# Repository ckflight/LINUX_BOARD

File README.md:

# Embedded Linux Board Running Custom Linux Distribution

### Project Info:

 * AT91SAM9N12 Microprocessor with Memory Management Unit based Embedded Linux Board hardware and operating system files.
It has 133 MHz RAM and 4 Gb NAND Flash and QSPI Flash Interfaces.

 * This design is the custom version of SAM9N12-EK. The custom design has a RAM with different speed and latency, also it is using NAND Flash as a memory. Therefore, AT91Bootstrap Hardware initialization files must be customized accordingly. Briefly, the PLL and clocking settings as well as RAM latency values and NAND interface pinouts are changed accordingly. To see the details of the changes, please check **LINUX_BOARD/Linux_Files/At91bootstrap Files/at91sam9n12ek.c and .h** files. 

 * Buildroot is used for custom linux distribution. Check step by step guide below for details. Follow Ubuntu, u-boot and buildroot versions strictly as indicated below to make it compile properly.

### Final Board Screenshots:

### Important Notes: 

 * Use TeraTerm on Windows or Picocom on Mac OSx to be able to set the baud rate to 118200 8bit no parity 1 stop. The reason of this baudrate is that, In AT91Bootstrap, cpu clock is configured from 400MHz to 300MHz for changing RAM speed from 133MHz to 100MHz. Since PLL multipliers are not strickly generating 300 and 100 MHz, the actual speeds are 301.333 MHz and 101.333. This main clock difference changes all other peripherals' clocking. As result of this, characters are not received correctly when the baudrate is set to 115200. When the baudrate is set to 118200 on HOST side, the hardware and the HOST side can talk without any issue. **(However in buildroot, u-boot and AT91Bootstrap files the uart is configured to 115200 8N1 no parity)**
 
 * The steps below are tested with UBUNTU 16.04.6 and 18.04.2 LTS.
 
### STEP BY STEP GUIDE FOR FLASHING BOARD TO RUN LINUX 
  
#### 1. This part describes how board is connected over USB and what commands needed to see on sam_ba program

   If linux board is new and fresh then connect over usb to linux virtual computer
   If linux board is flashed previously with files then connect nandflash's pin41 to ground and plug usb
   Linux will see device as /dev/ttyACM0 but sam_ba cannot see so type command (It is required every time): 
   
   	sudo chmod a+rw /dev/ttyACM0
   
   Or add read write permission to usb device to not write above command every time.To do that, 
   go to /etc/udev/rules.d and create a rule file such as myusb.rules file and add the line
 	
	sudo nano /etc/udev/rules.d/filename.rules
	KERNEL=="ttyACM[0-9]*",MODE="0666"

    Now sam-ba can see board as /dev/ttyACM0

#### 2. Before start install these libraries:

	1. sudo apt install libncurses5 libncursesw5-dev libncurses5-dev
	2. sudo apt install make
	3. sudo apt install gcc-arm-linux-gnueabi
	4. sudo apt install gcc
	5. sudo apt install g++
	6. sudo apt install python
        (these might no be needed)
	7. sudo apt install make-guile
	8. sudo apt install gcc-multilib
	9. sudo apt install gcc-arm*

	Files required for board and in this part they will be created:
	A. AT91SAMBOOTSTRAP 	(Initialises SAM9N12E hardware like clock, nano interface scram gpio etc.)
	B. U-BOOT    		(Initialises SAM9N12E hardware clk, ram and etc.)
	C. BUILDROOT 		(LINUX KERNEL + ROOTFS (Our python c compiler nano etc apps are in rootfs) )

#### 2.1 How to compile and create at91sambootstrap files:
 
   I put at91bootstrap-3-3.8.tar.gz, it is the latest version and works
   unzip to Ubuntu and use it. For any case download link is below:
	
	http://repository.timesys.com/buildsources/a/at91bootstrap-3/

   Go to at91bootstrap-3-3.8 folder and change 

 	/at91bootstrap-3-3.8/board/at91sam9n12ek/at91sam9n12ek.c and .h files
 
   with

 	/at91bootstrap Files/at91sam9n12ek.c and .h
 
   Go to the at91bootstrap-3-3.8 folder location over terminal and apply commands

	1. make mrproper

	2. make at91sam9n12eknf_uboot_defconfig (nf means it will be loaded to nandflash, and u-boot means it will run u-boot)

	3. make menuconfig 			(this will open a configuration window)
	   3.1.Go to RAM Configuration and change RAM size to 64M
	   3.2 Go to NAND Flash configuration and change PMECC Error Correction Bits to 4bits, Sector to 512
	   3.3 Go to U-Boot Image Storage Setup and change External Ram Address to Load U-Boot Image from
               0x26F00000 to 0x22000000
	   3.4 Save an Alternate File and it will create .config file in at91bootstrap-3-3.8.(It is invisible nano .config opens if needed.)

	4. make CROSS_COMPILE=arm-linux-gnueabi-

	RESULT: The at91sam9n12ek-nandflashboot-uboot-3.8-beta1.bin file is ready in binaries file

#### 2.2 How to compile and create u-boot files:

   I put u-boot-2015.1.tar.gz to folder no need to download newer versions since include files naming are changed
   and they are not compiling without error. Unzip it to Ubuntu and use. For any case download link is below:

	 http://repository.timesys.com/buildsources/u/u-boot/

   Go to folder and change

	u-boot-2015.01/board/atmel/at91sam9n12ek/at91sam9n12ek.c file 
	with 
	/u-boot Files/at91sam9n12ek.c

    and

	u-boot-2015.01/include/configs/at91sam9n12ek.h file 
	with	
	/u-boot Files/at91sam9n12ek.h
	
    also For Ubuntu 16.04 gcc5.h, For Ubuntu 18.04 gcc7.h add (they have same code inside as well)

	/u-boot Files/compiler-gcc5.h or gcc.7 file
	to
	u-boot-2015.01/include/linux folder

   Go to u-boot-2015.01 folder with terminal and apply commands

	1. make mrproper

	2. make at91sam9n12ek_nandflash_defconfig (nandflash means this file will be written to nandflash)

	3. make CROSS_COMPILE=arm-linux-gnueabi-

	RESULT: The u-boot.bin is in u-boot-2015.01 folder

#### 2.3 How to compile and create build root files:
   
   I put buildroot-2015.2.tar.gz to folder and this version works. For any case download link is below:

	https://buildroot.org/downloads/

   Before start: Buildroot might create errors during compile. 
                 These are mostly package version collision type errors.
                 I look for error file and try to correct them. 
		 If i cannot then i disable that package with "make menuconfig" window.
                 Update when Ubuntu 16.04 is used: In buildroot-2015.2 it gave error i added correction files
		 Update when Ubuntu 18.04 is used: In buildroot-2015.2 it gave error i added correction files

   I used ready linux binary tree files with config files. (Read Linux Embedded Notes 5. DEVICE TREE: part for details of device tree .dts file)
  
   Go to /Buildroot_Files folder and copy 3 files from

	/Buildroot Files/
	to
	/buildroot-2015.02 main folder

   and then rename config-buildroot file as .config (it will be invisible after name change use terminal to see)

   Go to the buildroot-2015.02 folder and apply commands

	(To configure linux kernel to enable drivers use "make linux-menuconfig" command)
   	(for example wifi usb dongle drivers are enabled in linux menuconfig)

	1. make mrproper or make clean

	2. make menuconfig(if i want to add or change something)

	3. make

	RESULT: The files are in buildroot-2015.02/output/images

   Correction if Ubuntu 2016.04 is used (These can be applied when they occur during compilation): 
   	
	if an error not listed below happens first try to remove the installed package from "/output/build" and make again	

	a. ncrses:		copy the code in Buildroot_Correction/ncrse5.9_correction/MKlib_gen.sh 
                                and paste inside of (do not copy paste files itself copy paste code)
                                buildroot-2015.02/output/build/host-crse5.9/ncrse/base/Mklib_gen.sh
	
	c. host-mtd1.5.1: 	(DO THIS TO HOST-MTD NOT MTD folder) copy the code Buildroot_Correction/mkfsutil_correction
                                and paste to (do not copy paste file)
				buildroot-2015.02/output/build/host-mtd1.5.1/mkfs.ubifs/hashtable

   Correction if Ubuntu 2018.04 is with gcc 5 used (These can be applied when they occur during compilation):
   (All error corrections are added below. If could not make it work use Ubuntu 16.04) 
   	
	a. libffi3.1: 		change Buildroot_Correction/libffi3.1_correction/automake file 
				with 
				buildroot-2015.02/output/host/user/bin/automake
	
	b. libglib2.42:         (DO THIS TO LIBGLIB NOT HOST-LIBGLIB folder) change Buildroot_Correction/libglib2.42_correction/gdate.c file
				with
				buildroot-2015.02/output/build/libglib2.42/glib/gdate.c

	c. lzop1.03:            copy the code Buildroot_Correction/lzop1.03_correction/miniacc.f file
                                and paste to (do not copy paste file)
				buildroot-2015.02/output/build/host-lzop1.03/src/miniacc.h

	d. ncrses:		copy the code Buildroot_Correction/ncrse5.9_correction/MKlib_gen.sh 
                                and paste to (do not copy paste file)
                                buildroot-2015.02/output/build/host-crse5.9/ncrse/base/Mklib_gen.sh
	
	e. host-mtd1.5.1: 	(DO THIS TO HOST-MTD NOT MTD folder) copy the code Buildroot_Correction/mkfsutil_correction
                                and paste to (do not copy paste file)
				buildroot-2015.02/output/build/host-mtd1.5.1/mkfs.ubifs/hashtable

#### 3. How to flash files to board:

   Memory locations of files
	
	* at91sam9n12ek-nandflashboot-uboot-3.8.bin -----> 0x00

	* u-boot.bin				     -----> 0x40000

	* at91sam9n12_sam_board_3.15.dtb	     -----> 0x180000

	* uImage.bin				     -----> 0x200000

	* rootfs.ubi				     -----> 0x800000

   Unzip /sam-ba to ubuntu and connect board over usb (see 1) then click connect.
   Select "NandFlash" tab and from Scripts select "Enable NandFlash" click execute button.
   It should print as below:

	-I- NANDFLASH::Init (trace level : 4)
	-I- Loading applet applet-nandflash-sam9n12.bin at address 0x20000000
	-I- Memory Size : 0x20000000 bytes
	-I- Buffer address : 0x20011404
	-I- Buffer size: 0x20000 bytes
	-I- Applet initialization done

   Then again from Scripts select "Pmecc configuration" click execute button.
   (I think it reads nandflash auto but do anyway because when wrong parameters selected it gives error.)
   Select ECC bit: 4
   Select Sector size: 512

   It should print as below:
	-I- Ecc type is 2 Ecc Status is 2
	-I- Configure trimffs 0
	-I- PMECC c0082805 to be Configured
	-I- Pmecc header configration successful
	-I- PMECC configure c0082805   

#### 3.1. Set Address to 0x00 and from Scripts select "Send Boot File" click execute button.  
      Select at91sam9n12ek-nandflashboot-uboot-3.8.bin file and click open.

      It should print as below:
	   -I- Sending boot file done.

   From now on execute button will not be used. Rest of the files will send with
   "Send File Name" folder selector and address setting.

#### 3.2. Set Address to 0x40000 and from "Send File Name" folder selector 
      select "u-boot.bin" file and click "Send File".

      It should print as below:
	   -I- Send File /home/ck/Desktop/u-boot.bin at address 0x40000
	   GENERIC::SendFile /home/ck/Desktop/u-boot.bin at address 0x40000
	   -I- File size : 0x5CD30 byte(s)
	   -I- 	Writing: 0x20000 bytes at 0x40000 (buffer addr : 0x20011404)
	   -I- 	0x20000 bytes written by applet
	   -I- 	Writing: 0x20000 bytes at 0x60000 (buffer addr : 0x20011404)
	   -I- 	0x20000 bytes written by applet
	   -I- 	Writing: 0x1CD30 bytes at 0x80000 (buffer addr : 0x20011404)
	   -I- 	0x1CD30 bytes written by applet

#### 3.3. Set Address to 0x180000 and from "Send File Name" folder selector 
      select "at91sam9n12_sam_board_3.15.dtb" file and click "Send File".
      
      It should print as below:
	   -I- Send File /home/ck/Desktop/at91sam9n12_sam_board_3.15.dtb at address 0x180000
	   GENERIC::SendFile /home/ck/Desktop/at91sam9n12_sam_board_3.15.dtb at address 0x180000
	   -I- File size : 0x2966 byte(s)
	   -I- 	Writing: 0x2966 bytes at 0x180000 (buffer addr : 0x20011404)
	   -I- 	0x20000 bytes written by applet

#### 3.4. Set Address to 0x200000 and from "Send File Name" folder selector 
      select "uImage.bin" file and click "Send File".
      
      It should print as below:

	   -I- Send File /home/ck/Desktop/uImage.bin at address 0x200000
	   GENERIC::SendFile /home/ck/Desktop/uImage.bin at address 0x200000
	   -I- File size : 0x2B91F0 byte(s)
	   -I- 	Writing: 0x20000 bytes at 0x200000 (buffer addr : 0x20011404)
	   -I- 	0x20000 bytes written by applet
	   ... goes like this
	   -I- 	Writing: 0x191F0 bytes at 0x4A0000 (buffer addr : 0x20011404)
	   -I- 	0x191F0 bytes written by applet

#### 3.5. Set Address to 0x800000 and from "Send File Name" folder selector 
      select "rootfs.ubi" file and click "Send File".

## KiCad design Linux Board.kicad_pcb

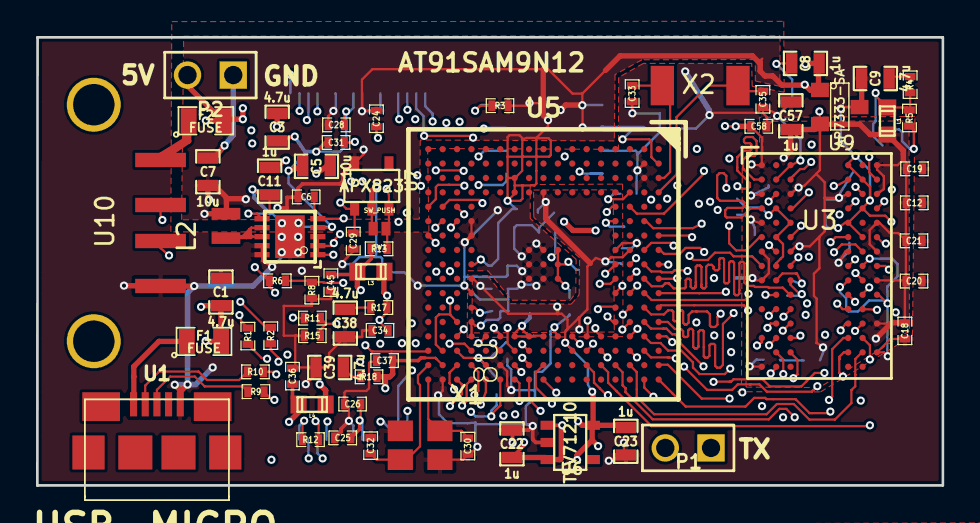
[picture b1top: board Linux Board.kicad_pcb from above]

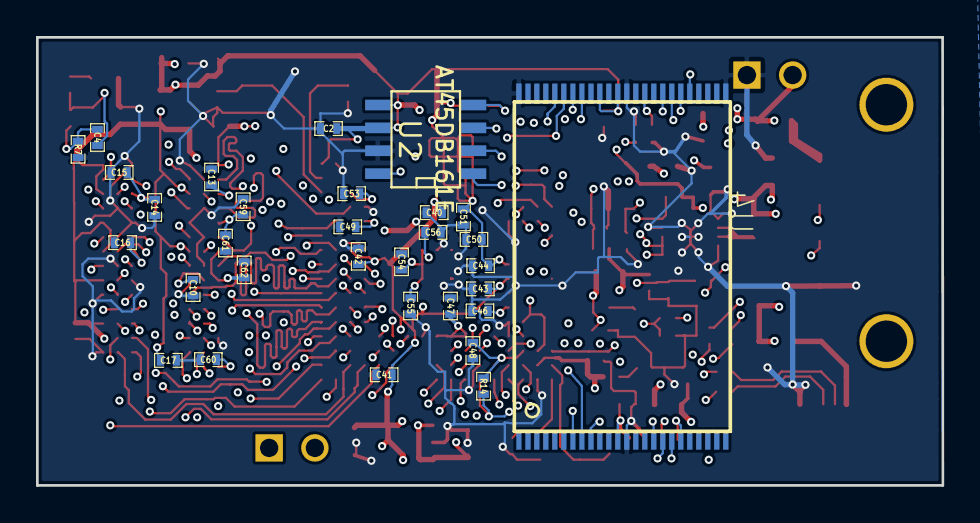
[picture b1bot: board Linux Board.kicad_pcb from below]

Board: 4 copper layers, 50.3 x 24.9 mm, 98 parts (31 on the bottom side), 94 nets.

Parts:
C1, C3, C9, C38, C39: 4.7u; SM0603_Capa
C2, C4, C10, C12, C13, C14, C15, C16, C17, C18, C19, C20, C21, C24, C25, C26, C28, C29, C31, C34, C36, C37, C40, C41, C42, C43, C44, C45, C46, C47, C48, C49, C50, C51, C53, C54, C55, C56, C58, C59, C60, C61, C62: 100n; SM0402_c
C5, C7: 10u; SM0603_Capa
C6: 100p; SM0402_c
C8, C11, C22, C23, C57: 1u; SM0603_Capa
C30, C32, C33, C35: 15p; SM0402_c
F1, F2: FUSE; SM0805
L1, L3, L4: 10u/100mA; c_0603
L2: 1.0u/1.5A; VLS201612E
P1, P2: CONN_2; PIN_ARRAY_2X1
R1, R2, R9, R10: 27; SM0402_r
R3, R12, R14: 470k; SM0402_r
R4, R17, R18: 1; SM0402_r
R5, R7: 1.5k; SM0402_r
R6: 450k; SM0402_r
R8: 100k; SM0402_r
R11, R15: 0; SM0402_r
R13: 10k; SM0402_r
SW1: SW_PUSH; S_JUMPER_2
U1: USB-MICRO; MICRO-B_USB
U2: AT45DB161E; SO8E
U3: W9751G6KB; WBGA-84
U4: PAM2321; DFN10-3X3
U5: AT91SAM9N12; lfbga217-std
U6: TLV71210; SOT23-5
U7: APX823; SOT23-5
U8: S34ML04G2; TSOP48
U9: AP7333-SA; SOT23
U10: USB-A; USB-A-SMD
X1: 16MHz; TSX-3225
X2: 32.768kHz; ABS10

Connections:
1V: C23.1, C36.1, C40.1, C41.1, C42.1, C43.1, L4.1, U5.C8, U5.G15, U5.J4, U5.P10, U6.5
3V3: C2.1, C6.1, C7.1, C8.1, C22.1, C24.1, C25.1, C26.1, C28.1, C44.1, C45.1, C46.1, C47.1, C48.1, C49.1, C50.1, C51.1, C53.1, L2.2, L3.1, R3.2, R6.1, R11.2, R12.1, R13.1, R14.2, U2.5, U2.6, U5.A2, U5.C4, U5.D6, U5.J14, U5.K14, U5.L3, U5.L4, U5.L14, U5.N16, U5.P9, U5.P12, U5.R15, U6.1, U6.3, U7.5, U8.12, U8.34, U8.37, U8.39, U9.1
5V: C1.1, C3.1, C5.1, C11.1, F1.2, F2.2, P2.2, U4.1, U4.2, U4.3
+1.8V: C12.1, C13.1, C14.1, C15.1, C16.1, C17.1, C18.1, C19.1, C20.1, C21.1, C54.1, C55.1, C56.1, C57.1, C58.1, C59.1, C60.1, C61.1, C62.1, L1.1, U3.A1, U3.A9, U3.C1, U3.C3, U3.C7, U3.C9, U3.E1, U3.E9, U3.G1, U3.G3, U3.G7, U3.G9, U3.J1, U3.J9, U3.M9, U3.R1, U5.H8, U5.H9, U5.H10, U9.2
/A2: U3.M8, U5.F16
/A3: U3.M3, U5.B17
/A4: U3.M7, U5.A17
/A5: U3.N2, U5.F15
/A6: U3.N8, U5.E16
/A7: U3.N3, U5.D16
/A8: U3.N7, U5.E15
/A9: U3.P2, U5.G14
/A10: U3.P8, U5.C16
/A11: U3.P3, U5.F14
/A13: U3.P7, U5.A16
/A14: U3.R2, U5.C15
/A16/BA0: U3.L2, U5.B15
/A17/BA1: U3.L3, U5.E14
/CAS: U3.L7, U5.D9
/D0: U3.G8, U5.B14
/D1: U3.G2, U5.A14
/D2: U3.H7, U5.C14
/D3: U3.H3, U5.D13
/D4: U3.H1, U5.C13
/D5: U3.H9, U5.B13
/D6: U3.F1, U5.A13
/D7: U3.F9, U5.C12
/D8: U3.C8, U5.D12
/D9: U3.C2, U5.B12
/D10: U3.D7, U5.C11
/D11: U3.D3, U5.D11
/D12: U3.D1, U5.A12
/D13: U3.D9, U5.B11
/D14: U3.B1, U5.A11
/D15: U3.B9, U5.C10
/D16: U5.L15, U8.29
/D17: U5.L16, U8.30
/D18: U5.L17, U8.31
/D19: U5.K17, U8.32
/D20: U5.K16, U8.41
/D21: U5.K15, U8.42
/D22: U5.J17, U8.43
/D23: U5.J16, U8.44
/DQM0: U3.F3, U5.C9
/DQM1: U3.B3, U5.A8
/DQS0: U3.F7, U5.B8
/DQS1: U3.B7, U5.A7
/DRXD: P1.2, U5.R5
/DTXD: P1.1, U5.R6
/MISO0: U2.8, U5.T5
/MOSI0: U2.1, U5.T6
/NANDALE: U5.M15, U8.17
/NANDCLE: U5.M14, U8.16
/NANDCS: U5.P16, U8.9
/NANDOE: U5.P15, U8.8
/NANDWE: U5.N14, U8.18
/NCS1: U3.L8, U5.C5
/NPCS0: R3.1, U2.4, U5.U7
/NWAIT: R14.1, U5.M17, U8.7
/RAS: U3.K7, U5.B9
/SCK0: U2.2, U5.U5
/SDA10: U3.M2, U5.B6
/SDCK: U3.J8, U5.A10
/SDCKE: U3.K2, U5.D10
/SDCKN: U3.K8, U5.A9
/SDWE: U3.K3, U5.B10
/VDD_OSC: C34.1, L3.2, R17.2, U5.R14
/VDD_PLL: C37.1, L4.2, R18.2, U5.T16
GND: C1.2, C2.2, C3.2, C5.2, C7.2, C8.2, C9.2, C10.2, C11.2, C12.2, C13.2, C14.2, C15.2, C16.2, C17.2, C18.2, C19.2, C20.2, C21.2, C22.2, C23.2, C24.2, C25.2, C26.2, C28.2, C29.2, C30.1, C31.2, C32.1, C33.2, C34.2, C35.2, C36.2, C37.2, C38.2, C39.2, C40.2, C41.2, C42.2, C43.2, C44.2, C45.2, C46.2, C47.2, C48.2, C49.2, C50.2, C51.2, C53.2, C54.2, C55.2, C56.2, C57.2, C58.2, C59.2, C60.2, C61.2, C62.2, P2.1, R7.2, R8.1, R15.1, SW1.2, U1.5, U2.7, U3.A3, U3.A7, U3.B2, U3.B8, U3.D2, U3.D8, U3.E3, U3.E7, U3.F2, U3.F8, U3.H2, U3.H8, U3.J3, U3.J7, U3.K9, U3.N1, U3.P9, U4.4, U4.6, U4.9, U4.10, U4.EXP, U5.B2, U5.B3, U5.D5, U5.D8, U5.H14, U5.J8, U5.J9, U5.J10, U5.K8, U5.K9, U5.K10, U5.M16, U5.P6, U5.P7, U5.P11, U5.P13, U5.P14, U5.T17, U6.2, U7.2, U8.13, U8.25, U8.36, U8.48, U9.3, U10.4, X1.2, X1.4
unnamed: C4.2, C10.1, R5.2, R7.1, U3.J2
unnamed: L2.1, U4.7, U4.8
unnamed: C38.1, R17.1
unnamed: C6.2, R6.2, R8.2, U4.5
unnamed: F2.1, U10.1
unnamed: R2.1, U5.N17
unnamed: R1.1, U5.P17
unnamed: R12.2, U8.19
unnamed: C32.2, U5.U16, X1.1
unnamed: C39.1, R18.1
unnamed: C9.1, R4.2
unnamed: F1.1, U1.1
unnamed: R10.1, U5.R16
unnamed: R9.1, U5.R17
unnamed: R11.1, R15.2, U5.U15
unnamed: C31.1, R13.2, SW1.1, U7.3
unnamed: C30.2, U5.U17, X1.3
unnamed: C4.1, L1.2, R4.1, R5.1
unnamed: C35.1, U5.A4, X2.2
unnamed: C33.1, U5.A3, X2.1
USBDM: R10.2, U1.2
USBDP: R9.2, U1.3
USBHM: R2.2, U10.2
USBHP: R1.2, U10.3
~RESET: C29.1, U2.3, U5.R13, U5.T15, U7.1

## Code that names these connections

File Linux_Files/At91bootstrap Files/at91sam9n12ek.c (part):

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
	/* Configure nand pins */
	const struct pio_desc nand_pins_lo[] = {
		{"NANDOE",	AT91C_PIN_PD(0), 			0,		PIO_PULLUP, PIO_PERIPH_A},
		{"NANDWE",	AT91C_PIN_PD(1), 			0,		PIO_PULLUP, PIO_PERIPH_A},
		{"NANDALE",	AT91C_PIN_PD(2), 			0,		PIO_PULLUP, PIO_PERIPH_A},
		{"NANDCLE",	AT91C_PIN_PD(3), 			0,		PIO_PULLUP, PIO_PERIPH_A},
		{"NANDCS",	CONFIG_SYS_NAND_ENABLE_PIN,	1, 		PIO_PULLUP, PIO_OUTPUT},
		{"D16",		AT91C_PIN_PD(6), 			0,		PIO_PULLUP, PIO_PERIPH_A},
		{"D17",		AT91C_PIN_PD(7), 			0,		PIO_PULLUP, PIO_PERIPH_A},
		{"D18",		AT91C_PIN_PD(8), 			0,		PIO_PULLUP, PIO_PERIPH_A},
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

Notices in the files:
Linux_Files/At91bootstrap Files/at91sam9n12ek.c:
Copyright (c) 2008, Atmel Corporation
All rights reserved.
